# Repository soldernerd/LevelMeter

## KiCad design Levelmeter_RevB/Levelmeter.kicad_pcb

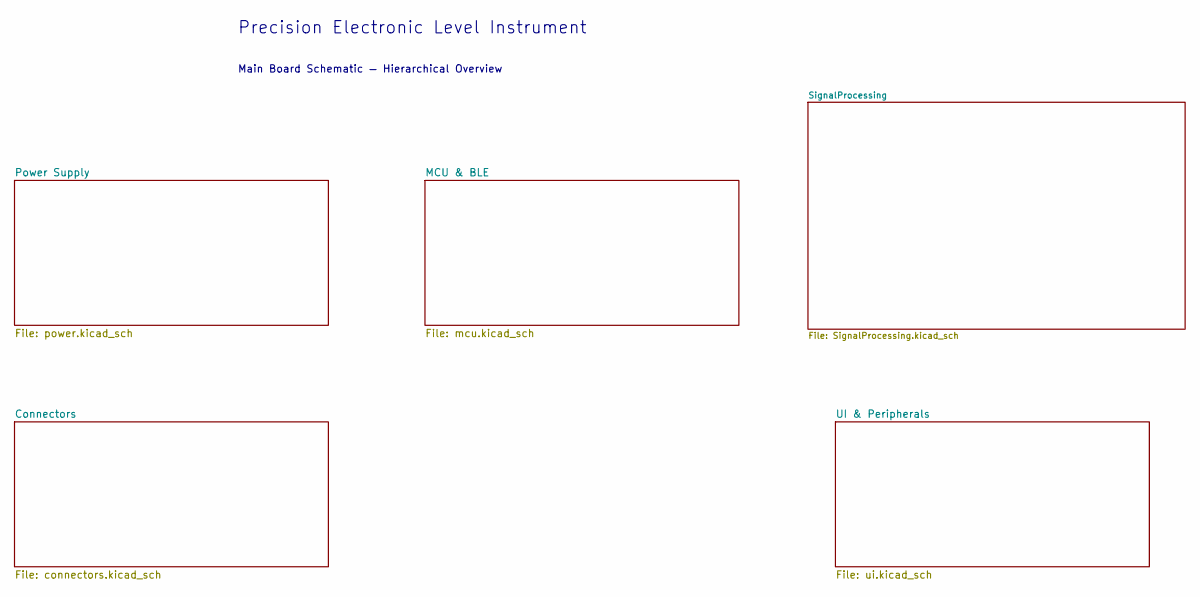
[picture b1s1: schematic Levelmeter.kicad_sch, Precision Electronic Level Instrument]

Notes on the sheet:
Main Board Schematic — Hierarchical Overview
Precision Electronic Level Instrument

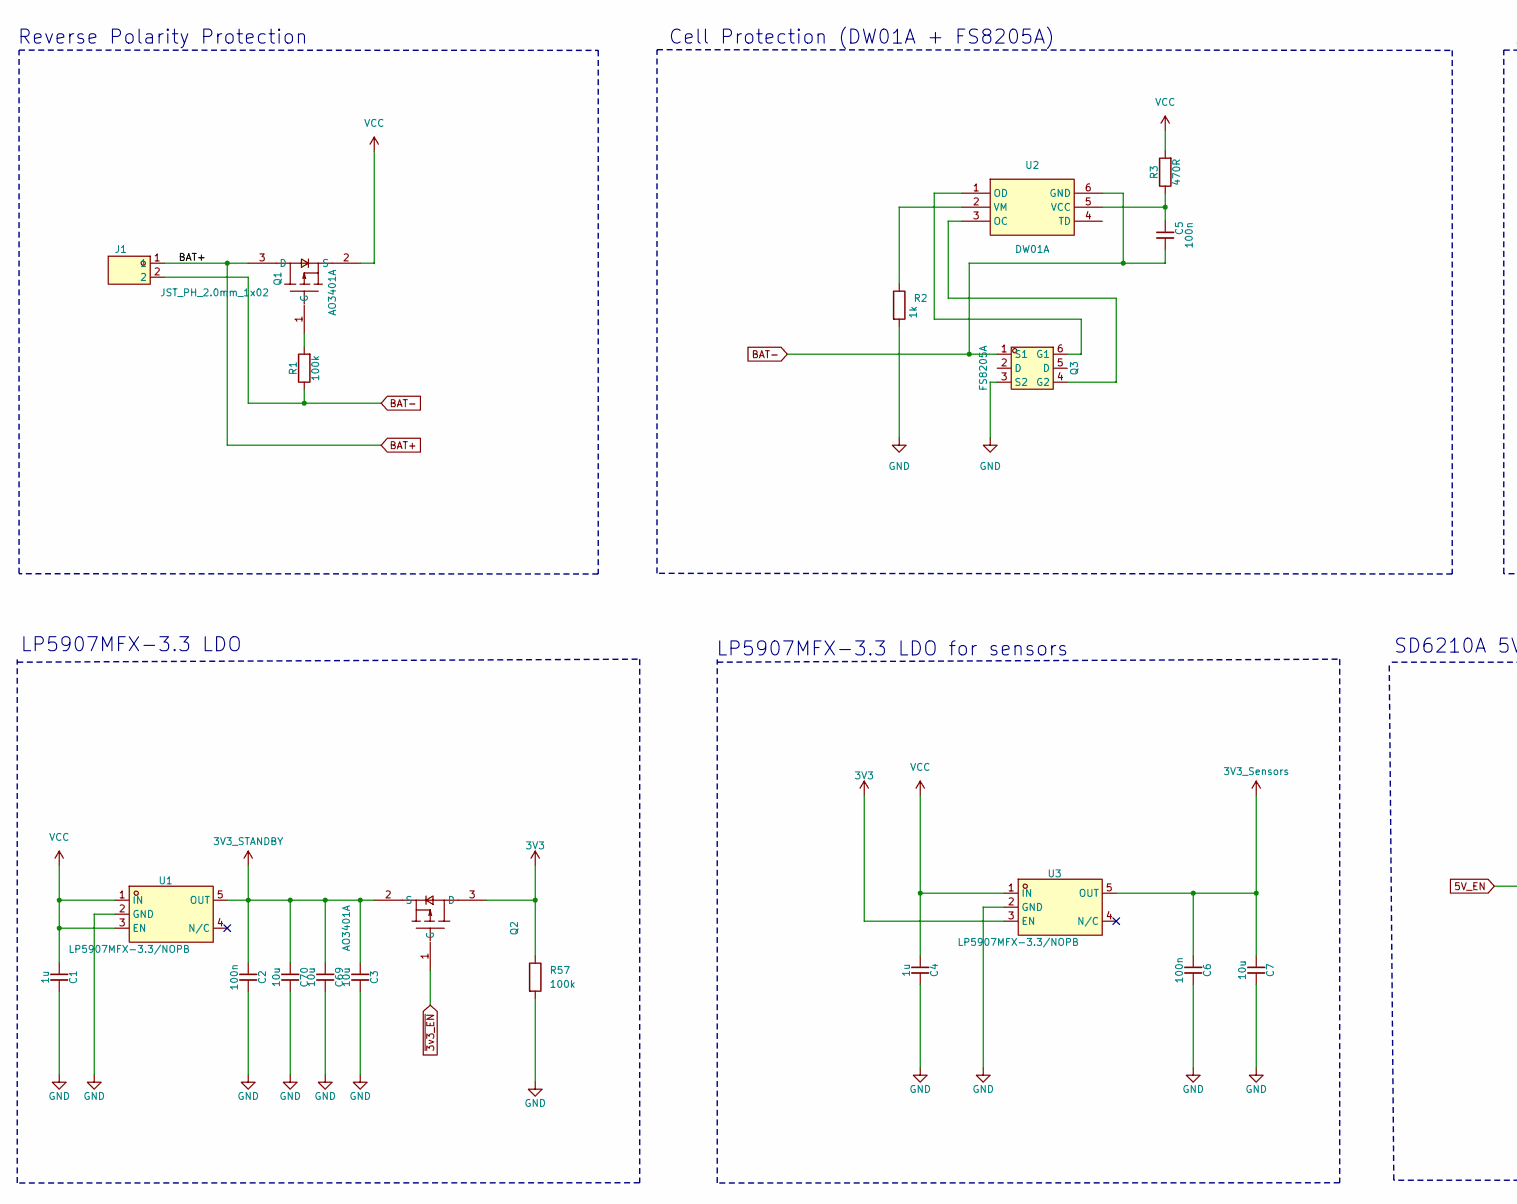
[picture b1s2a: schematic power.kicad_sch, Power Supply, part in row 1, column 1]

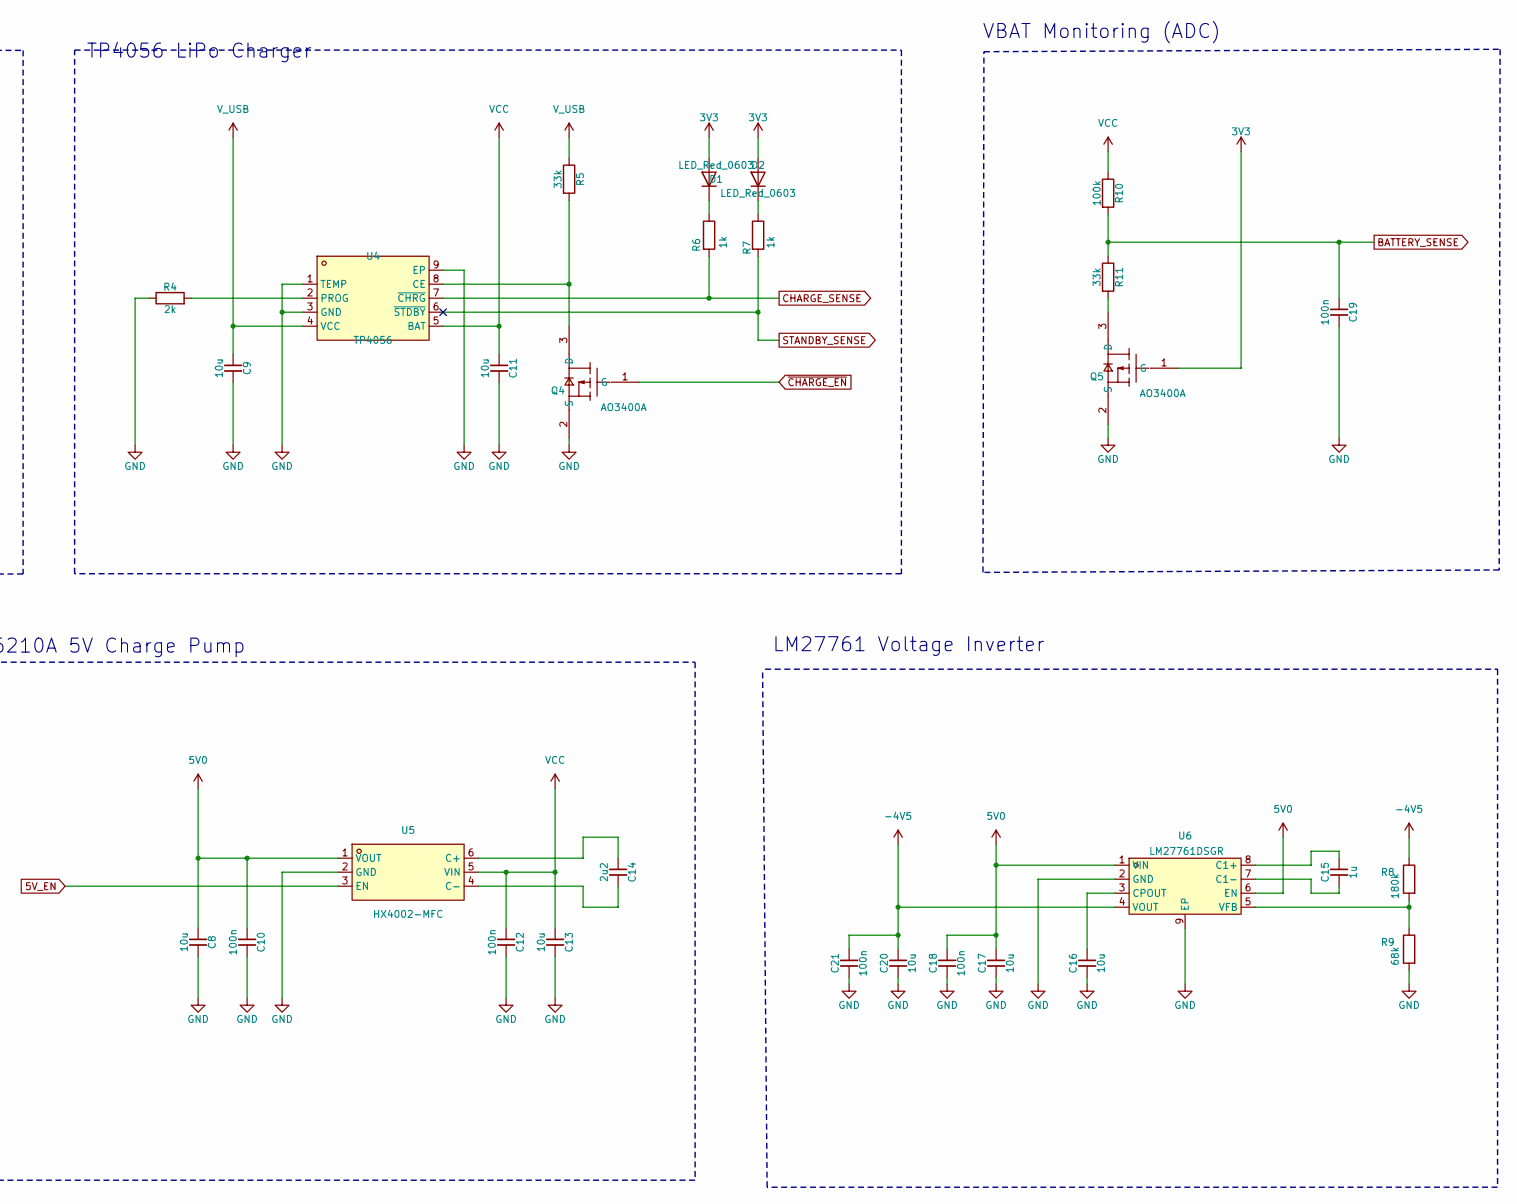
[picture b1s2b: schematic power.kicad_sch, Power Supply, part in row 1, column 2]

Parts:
C1, C4, C15: 1u; C_0805; Voltage 50V; MPN CL21B105KBFNNNE; LCSC C28323
C2, C5, C6, C10, C12, C18, C19, C21: 100n; C_0603; Voltage 50V; MPN CC0603KRX7R9BB104; LCSC C14663
C3, C7, C8, C9, C11, C13, C16, C17, C20, C69, C70: 10u; C_0805; Voltage 50V; MPN GRM21BR61H106KE43L; LCSC C440198
C14: 2u2; C_0805; Voltage 50V; MPN CL21A225KBQNNNE; LCSC C377773
D1, D2: LED_Red_0603; LED_0603; MPN KT-0603R; LCSC C2286
J1: JST_PH_2.0mm_1x02; MPN B2B-PH-K-S; LCSC C131337
Q1, Q2: AO3401A; SOT-23-3; MPN AO3401A; LCSC C15127
Q3: FS8205A; SOT-23-6; MPN FS8205A; LCSC C2830320
Q4, Q5: AO3400A; SOT-23-3; MPN AO3400A; LCSC C20917
R1, R10, R57: 100k; R_0603; MPN 0603WAF1003T5E; LCSC C25803
R2, R6, R7: 1k; R_0603; MPN 0603WAF1001T5E; LCSC C21190
R3: 470R; R_0603; MPN 0603WAF4700T5E; LCSC C23179
R4: 2k; R_0603; MPN 0603WAF2001T5E; LCSC C22975
R5, R11: 33k; R_0603; MPN 0603WAF3302T5E; LCSC C4216
R8: 180k; R_0603; MPN 0603WAF1803T5E; LCSC C22827
R9: 68k; R_0603; MPN 0603WAF6802T5E; LCSC C23231
U1, U3: LP5907MFX-3.3/NOPB; SOT-23-5; MPN LP5907MFX-3.3/NOPB; LCSC C80670
U2: DW01A; SOT-23-6; MPN DW01A; LCSC C351410
U4: TP4056; ESOP-8; MPN TP4056; LCSC C382139
U5: HX4002-MFC; SOT-23-6; MPN HX4002-MFC; LCSC C172354
U6: LM27761DSGR; WSON-8-2x2-EP; MPN LM27761DSGR; LCSC C129351

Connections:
3V3: D1.2 (A), D2.2 (A), Q2.3 (D), Q5.1 (G), R57.1, U3.3 (EN); also elsewhere on the board
3V3_STANDBY: C2.1, C3.1, C69.1, C70.1, Q2.2 (S), U1.5 (OUT); also elsewhere on the board
3V3_Sensors: C6.1, C7.1, U3.5 (OUT); also elsewhere on the board
5V0: C8.1, C10.1, C17.1, C18.1, U5.1 (VOUT), U6.1 (VIN), U6.6 (EN); also elsewhere on the board
5V_EN: U5.3 (EN); also elsewhere on the board
~3v3_EN: Q2.1 (G); also elsewhere on the board
-4V5: C20.1, C21.1, R8.1, U6.4 (VOUT); also elsewhere on the board
BAT+: J1.1, Q1.3 (D)
BAT-: C5.2, J1.2, Q3.1 (S1), R1.1, U2.6 (GND)
BATTERY_SENSE: C19.1, R10.2, R11.1; also elsewhere on the board
CHARGE_SENSE: R6.2, U4.7 (~CHRG); also elsewhere on the board
GND: C1.2, C2.2, C3.2, C4.2, C6.2, C7.2, C8.2, C9.2, C10.2, C11.2, C12.2, C13.2, C16.2, C17.2, C18.2, C19.2, C20.2, C21.2, C69.2, C70.2, Q3.3 (S2), Q4.2 (S), Q5.2 (S), R2.2, R4.1, R9.2, R57.2, U1.2 (GND), U3.2 (GND), U4.1 (TEMP), U4.3 (GND), U4.9 (EP), U5.2 (GND), U6.2 (GND), U6.9 (EP); also elsewhere on the board
unnamed: D1.1 (K), R6.1
unnamed: D2.1 (K), R7.1
unnamed: Q1.1 (G), R1.2
unnamed: Q3.6 (G1), U2.1 (OD)
unnamed: Q3.4 (G2), U2.3 (OC)
unnamed: Q4.3 (D), R5.2, U4.8 (CE)
unnamed: Q5.3 (D), R11.2
unnamed: C5.1, R3.1, U2.5 (VCC)
unnamed: R2.1, U2.2 (VM)
unnamed: R4.2, U4.2 (PROG)
unnamed: C14.1, U5.6 (C+)
unnamed: C14.2, U5.4 (C-)
unnamed: C15.1, U6.8 (C1+)
unnamed: C15.2, U6.7 (C1-)
unnamed: C16.1, U6.3 (CPOUT)
unnamed: R8.2, R9.1, U6.5 (VFB)
STANDBY_SENSE: R7.2, U4.6 (~STDBY); also elsewhere on the board
VCC: C1.1, C4.1, C11.1, C12.1, C13.1, Q1.2 (S), R3.2, R10.1, U1.1 (IN), U1.3 (EN), U3.1 (IN), U4.5 (BAT), U5.5 (VIN)
V_USB: C9.1, R5.1, U4.4 (VCC); also elsewhere on the board
~CHARGE_EN: Q4.1 (G); also elsewhere on the board

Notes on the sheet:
LM27761 Voltage Inverter
LP5907MFX-3.3 LDO
VBAT Monitoring (ADC)
Cell Protection (DW01A + FS8205A)
TP4056 LiPo Charger
Reverse Polarity Protection
SD6210A 5V Charge Pump
LP5907MFX-3.3 LDO for sensors

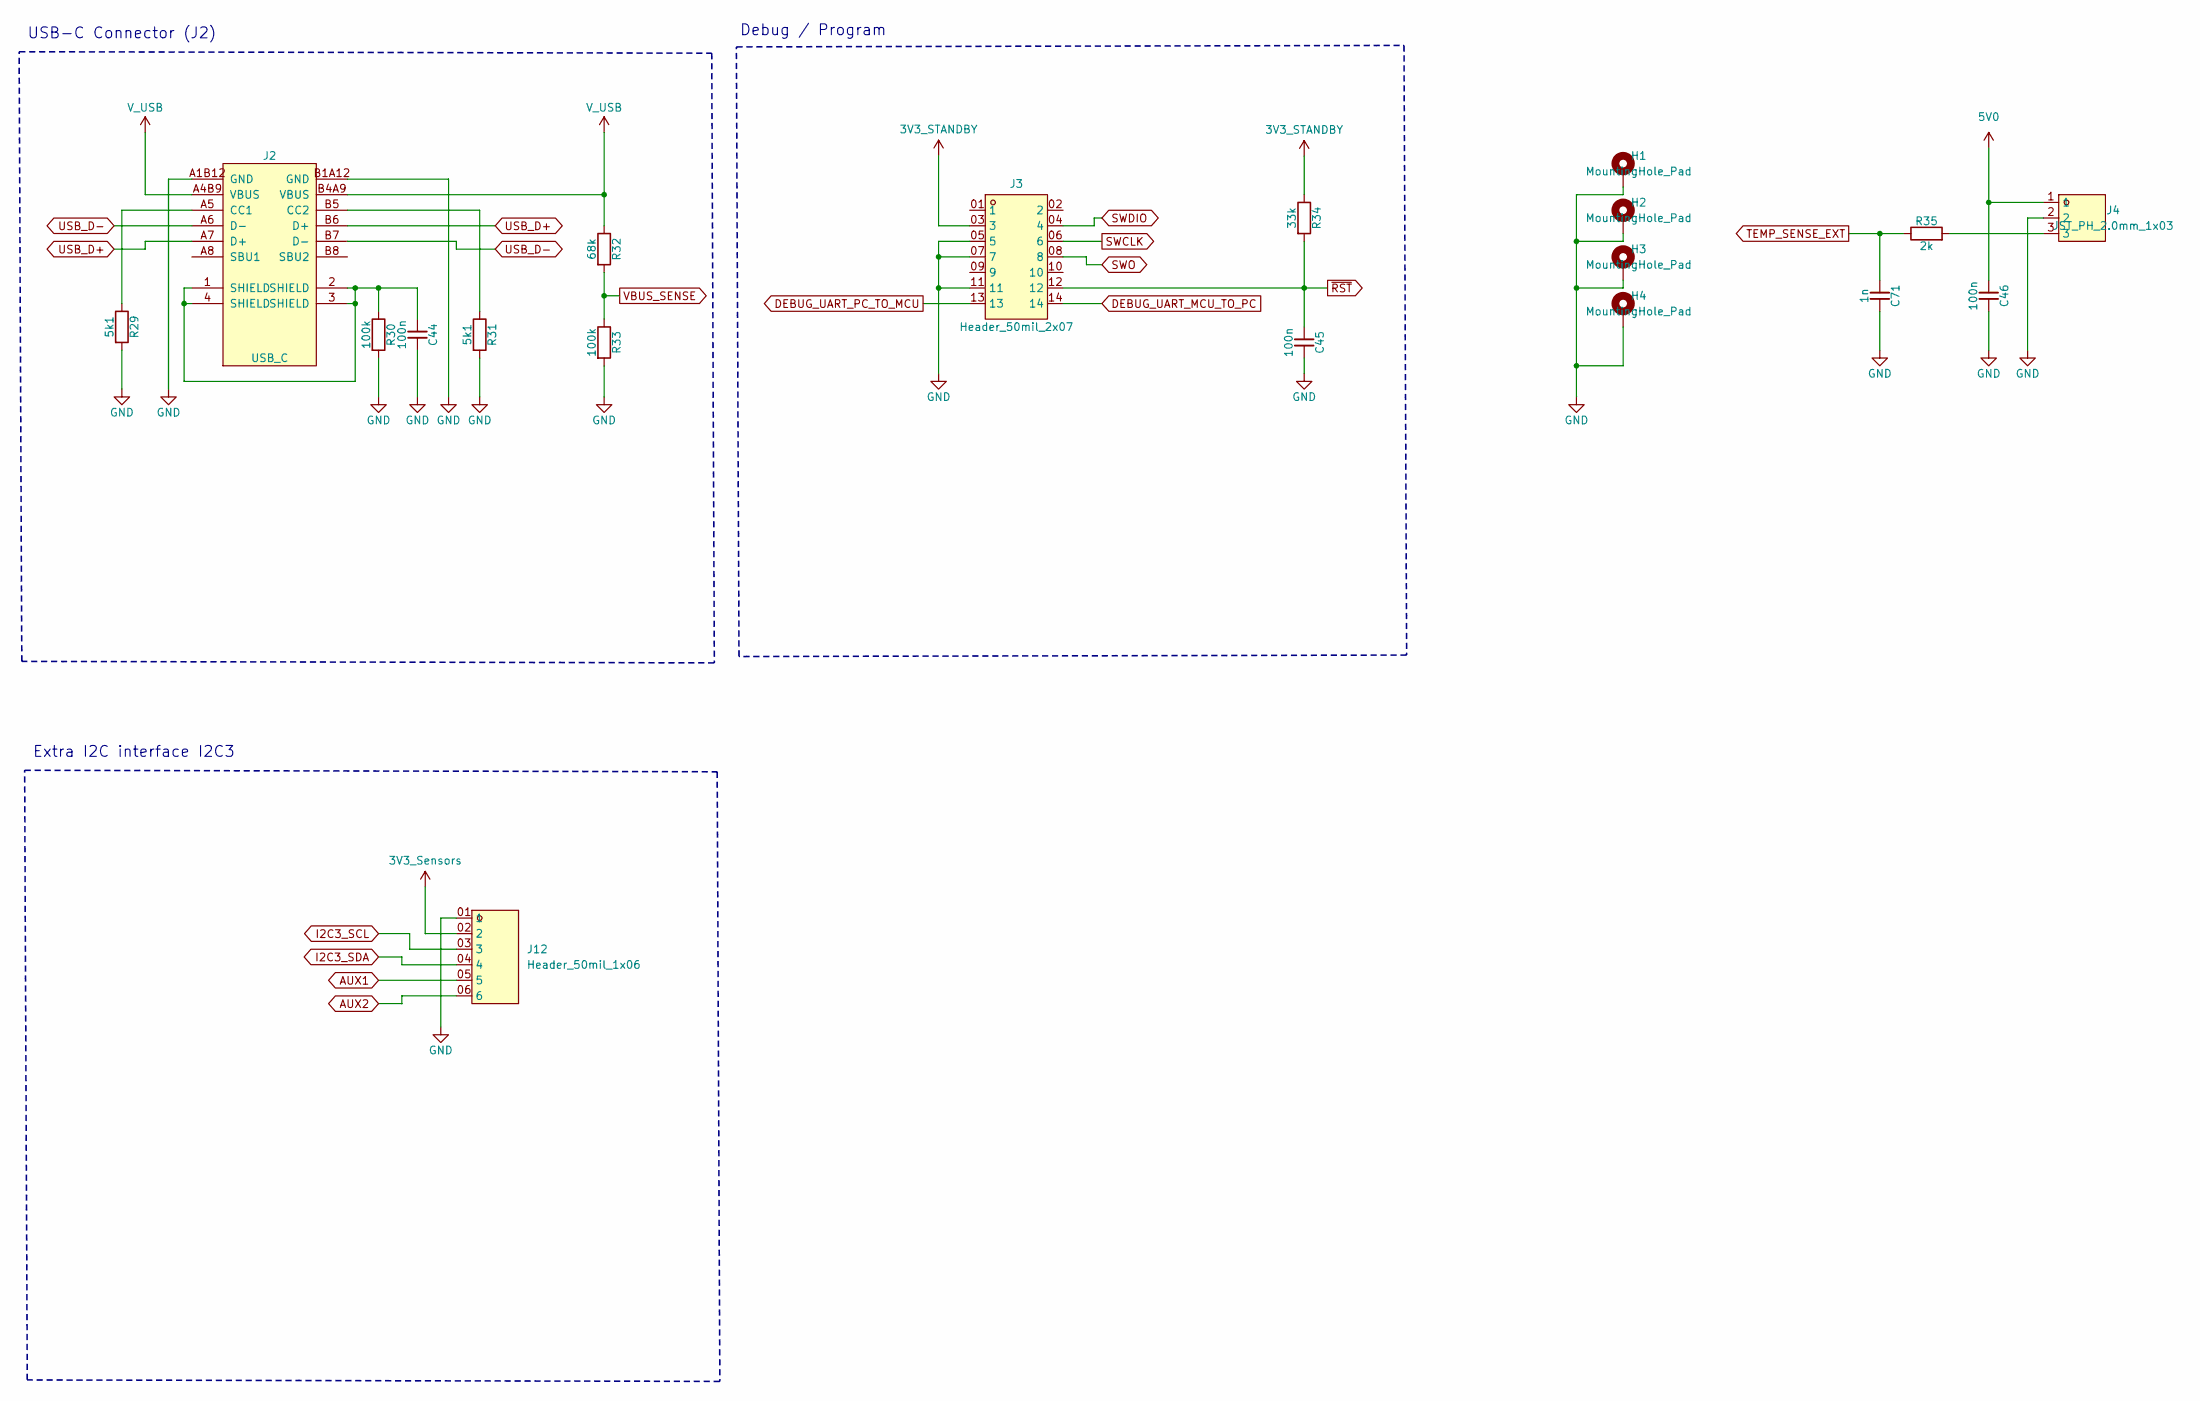
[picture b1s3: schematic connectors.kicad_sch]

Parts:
C44, C45, C46: 100n; C_0603; Voltage 50V; MPN CC0603KRX7R9BB104; LCSC C14663
C71: 1n; C_0603; Voltage 50V; MPN CL10B102KB8NNNC; LCSC C1588
H1, H2, H3, H4: MountingHole_Pad; MountingHole_3.2mm
J2: USB_C; MPN TYPE-C-31-M-12; LCSC C165948
J3: Header_50mil_2x07; LCSC C5563894
J4: JST_PH_2.0mm_1x03; MPN B3B-PH-K-S; LCSC C131339
J12: Header_50mil_1x06
R29, R31: 5k1; R_0603; MPN 0603WAF5101T5E; LCSC C23186
R30, R33: 100k; R_0603; MPN 0603WAF1003T5E; LCSC C25803
R32: 68k; R_0603; MPN 0603WAF6802T5E; LCSC C23231
R34: 33k; R_0603; MPN 0603WAF3302T5E; LCSC C4216
R35: 2k; R_0603; MPN 0603WAF2001T5E; LCSC C22975

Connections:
3V3_STANDBY: J3.03 (3), R34.1; also elsewhere on the board
3V3_Sensors: J12.02 (2); also elsewhere on the board
5V0: C46.1, J4.1; also elsewhere on the board
AUX1: J12.05 (5); also elsewhere on the board
AUX2: J12.06 (6); also elsewhere on the board
DEBUG_UART_MCU_TO_PC: J3.14; also elsewhere on the board
DEBUG_UART_PC_TO_MCU: J3.13; also elsewhere on the board
GND: C44.2, C45.2, C46.2, C71.2, H1.1 (1_1), H2.1 (1_1), H3.1 (1_1), H4.1 (1_1), J2.A1B12 (GND), J2.B1A12 (GND), J3.05 (5), J3.07 (7), J3.11, J4.2, J12.01 (1), R29.2, R30.2, R31.2, R33.2; also elsewhere on the board
I2C3_SCL: J12.03 (3); also elsewhere on the board
I2C3_SDA: J12.04 (4); also elsewhere on the board
unnamed: C44.1, J2.1 (SHIELD), J2.2 (SHIELD), J2.3 (SHIELD), J2.4 (SHIELD), R30.1
unnamed: J2.A5 (CC1), R29.1
unnamed: J2.B5 (CC2), R31.1
unnamed: J4.3, R35.2
SWCLK: J3.06 (6); also elsewhere on the board
SWDIO: J3.04 (4); also elsewhere on the board
SWO: J3.08 (8); also elsewhere on the board
TEMP_SENSE_EXT: C71.1, R35.1; also elsewhere on the board
USB_D+: J2.A7 (D+), J2.B6 (D+); also elsewhere on the board
USB_D-: J2.A6 (D-), J2.B7 (D-); also elsewhere on the board
VBUS_SENSE: R32.2, R33.1; also elsewhere on the board
V_USB: J2.A4B9 (VBUS), J2.B4A9 (VBUS), R32.1; also elsewhere on the board
~RST: C45.1, J3.12, R34.2; also elsewhere on the board

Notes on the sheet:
Extra I2C interface I2C3
USB-C Connector (J2)
Debug / Program

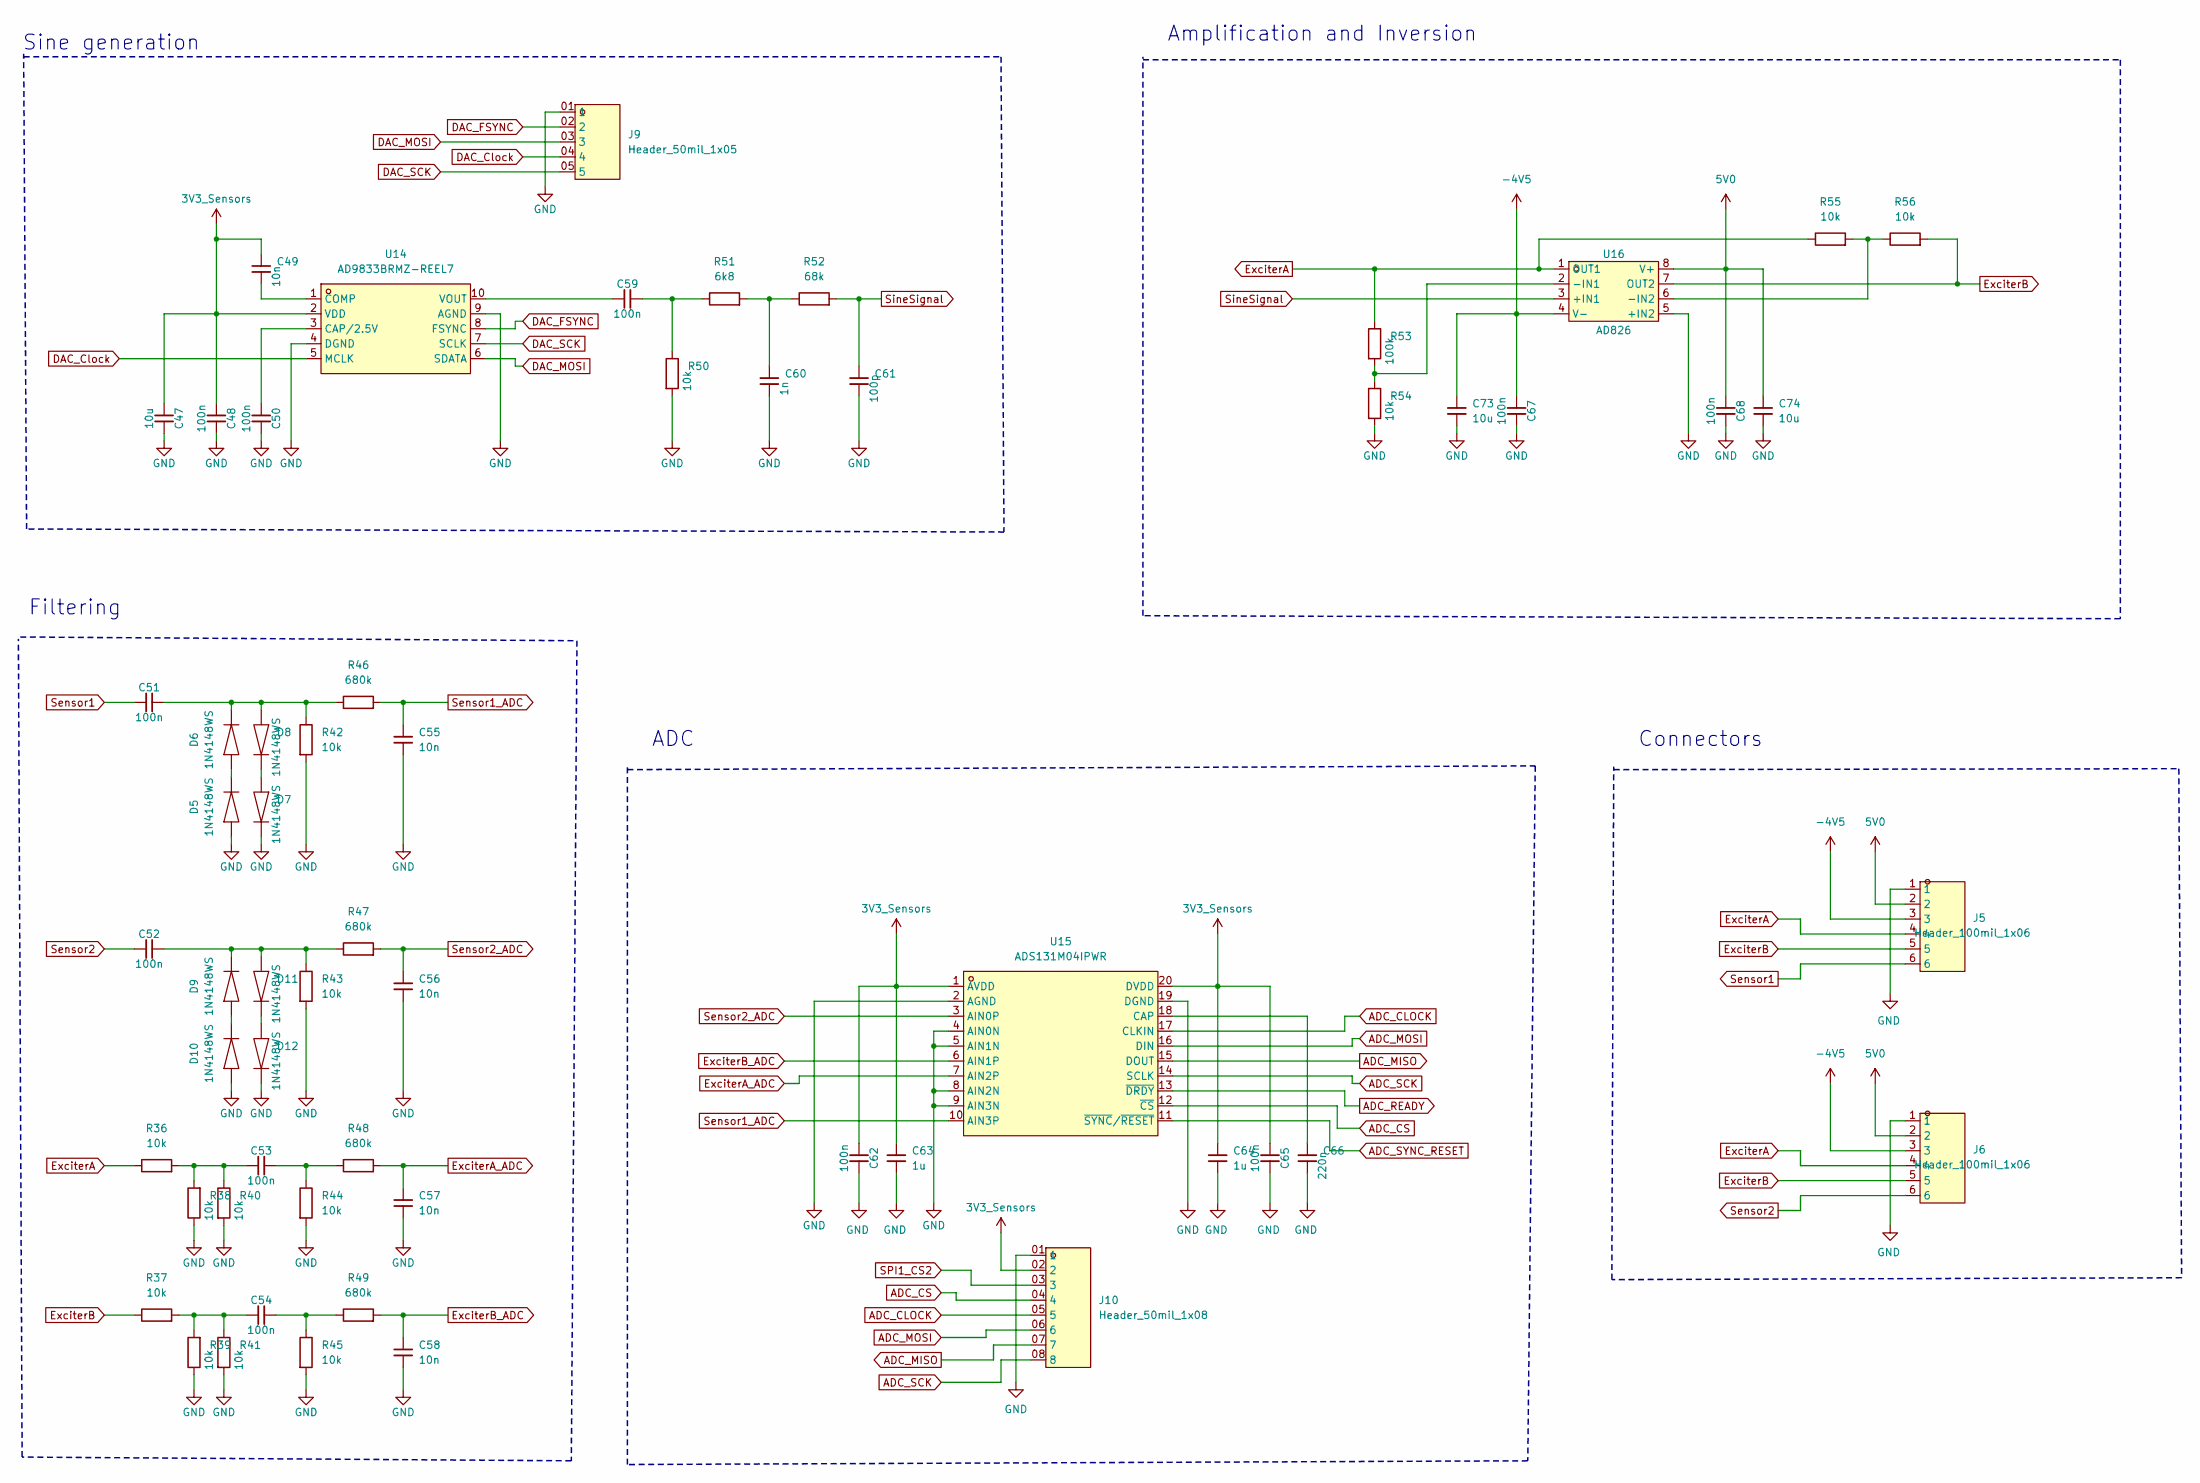
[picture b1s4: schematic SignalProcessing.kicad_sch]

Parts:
C47, C73, C74: 10u; C_0805; Voltage 50V; MPN GRM21BR61H106KE43L; LCSC C440198
C48, C50, C51, C52, C53, C54, C59, C62, C65, C67, C68: 100n; C_0603; Voltage 50V; MPN CC0603KRX7R9BB104; LCSC C14663
C49, C55, C56, C57, C58: 10n; C_0603; Voltage 50V; MPN 0603B103K500NT; LCSC C57112
C60: 1n; C_0603; Voltage 50V; MPN CL10B102KB8NNNC; LCSC C1588
C61: 100p; C_0603; Voltage 50V; MPN CL10C101JB8NNNC; LCSC C14858
C63, C64: 1u; C_0805; Voltage 50V; MPN CL21B105KBFNNNE; LCSC C28323
C66: 220n; C_0603; Voltage 25V; MPN CL10B224KA8NNNC; LCSC C21120
D5, D6, D7, D8, D9, D10, D11, D12: 1N4148WS; SOD-323; MPN 1N4148WS; LCSC C2128
J5, J6: Header_100mil_1x06; MPN A2541WV-6P; LCSC C225481
J9: Header_50mil_1x05
J10: Header_50mil_1x08
R36, R37, R38, R39, R40, R41, R42, R43, R44, R45, R50, R55, R56: 10k; R_0603; MPN 0603WAF1002T5E; LCSC C25804
R46, R47, R48, R49: 680k; R_0603; MPN 0603WAF6803T5E; LCSC C25822
R51: 6k8; R_0603; MPN 0603WAF6801T5E; LCSC C23212
R52: 68k; R_0603; MPN 0603WAF6802T5E; LCSC C23231
R53: 100k; R_0805; MPN 0805W8F1003T5E; LCSC C149504
R54: 10k; R_0805; MPN 0805W8F1002T5E; LCSC C17414
U14: AD9833BRMZ-REEL7; MSOP-10; MPN AD9833BRMZ-REEL7; LCSC C9652
U15: ADS131M04IPWR; TSSOP-20; MPN ADS131M04IPWR; LCSC C2862562
U16: AD826; SOIC-8; MPN AD826ARZ-REEL7; LCSC C114171

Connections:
3V3_Sensors: C47.1, C48.1, C49.1, C62.1, C63.1, C64.1, C65.1, J10.02 (2), U14.2 (VDD), U15.1 (AVDD), U15.20 (DVDD); also elsewhere on the board
5V0: C68.1, C74.1, J5.2, J6.2, U16.8 (V+); also elsewhere on the board
-4V5: C67.1, C73.1, J5.3, J6.3, U16.4 (V-); also elsewhere on the board
ADC_CLOCK: J10.05 (5), U15.17 (CLKIN); also elsewhere on the board
ADC_CS: J10.04 (4), U15.12 (~CS); also elsewhere on the board
ADC_MISO: J10.07 (7), U15.15 (DOUT); also elsewhere on the board
ADC_MOSI: J10.06 (6), U15.16 (DIN); also elsewhere on the board
ADC_READY: U15.13 (~DRDY); also elsewhere on the board
ADC_SCK: J10.08 (8), U15.14 (SCLK); also elsewhere on the board
ADC_SYNC_RESET: U15.11 (~SYNC/~RESET); also elsewhere on the board
DAC_Clock: J9.04 (4), U14.5 (MCLK); also elsewhere on the board
DAC_FSYNC: J9.02 (2), U14.8 (FSYNC); also elsewhere on the board
DAC_MOSI: J9.03 (3), U14.6 (SDATA); also elsewhere on the board
DAC_SCK: J9.05 (5), U14.7 (SCLK); also elsewhere on the board
ExciterA: J5.4, J6.4, R36.1, R53.1, R55.1, U16.1 (OUT1)
ExciterA_ADC: C57.1, R48.2, U15.7 (AIN2P)
ExciterB: J5.5, J6.5, R37.1, R56.2, U16.7 (OUT2)
ExciterB_ADC: C58.1, R49.2, U15.6 (AIN1P)
GND: C47.2, C48.2, C50.2, C55.2, C56.2, C57.2, C58.2, C60.2, C61.2, C62.2, C63.2, C64.2, C65.2, C66.2, C67.2, C68.2, C73.2, C74.2, D5.2 (A), D7.1 (K), D10.2 (A), D12.1 (K), J5.1, J6.1, J9.01 (1), J10.01 (1), R38.1, R39.1, R40.2, R41.2, R42.2, R43.2, R44.2, R45.2, R50.2, R54.2, U14.4 (DGND), U14.9 (AGND), U15.2 (AGND), U15.4 (AIN0N), U15.5 (AIN1N), U15.8 (AIN2N), U15.9 (AIN3N), U15.19 (DGND), U16.5 (+IN2); also elsewhere on the board
unnamed: C53.1, R36.2, R38.2, R40.1
unnamed: C53.2, R44.1, R48.1
unnamed: C54.1, R37.2, R39.2, R41.1
unnamed: C54.2, R45.1, R49.1
unnamed: C59.2, R50.1, R51.1
unnamed: C60.1, R51.2, R52.1
unnamed: D5.1 (K), D6.2 (A)
unnamed: C51.2, D6.1 (K), D8.2 (A), R42.1, R46.1
unnamed: D7.2 (A), D8.1 (K)
unnamed: D9.2 (A), D10.1 (K)
unnamed: C52.2, D9.1 (K), D11.2 (A), R43.1, R47.1
unnamed: D11.1 (K), D12.2 (A)
unnamed: C50.1, U14.3 (CAP/2.5V)
unnamed: C49.2, U14.1 (COMP)
unnamed: C59.1, U14.10 (VOUT)
unnamed: C66.1, U15.18 (CAP)
unnamed: R53.2, R54.1, U16.2 (-IN1)
unnamed: R55.2, R56.1, U16.6 (-IN2)
SPI1_CS2: J10.03 (3); also elsewhere on the board
Sensor1: C51.1, J5.6
Sensor1_ADC: C55.1, R46.2, U15.10 (AIN3P)
Sensor2: C52.1, J6.6
Sensor2_ADC: C56.1, R47.2, U15.3 (AIN0P)
SineSignal: C61.1, R52.2, U16.3 (+IN1)

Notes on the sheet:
ADC
Connectors
Filtering
Amplification and Inversion
Sine generation

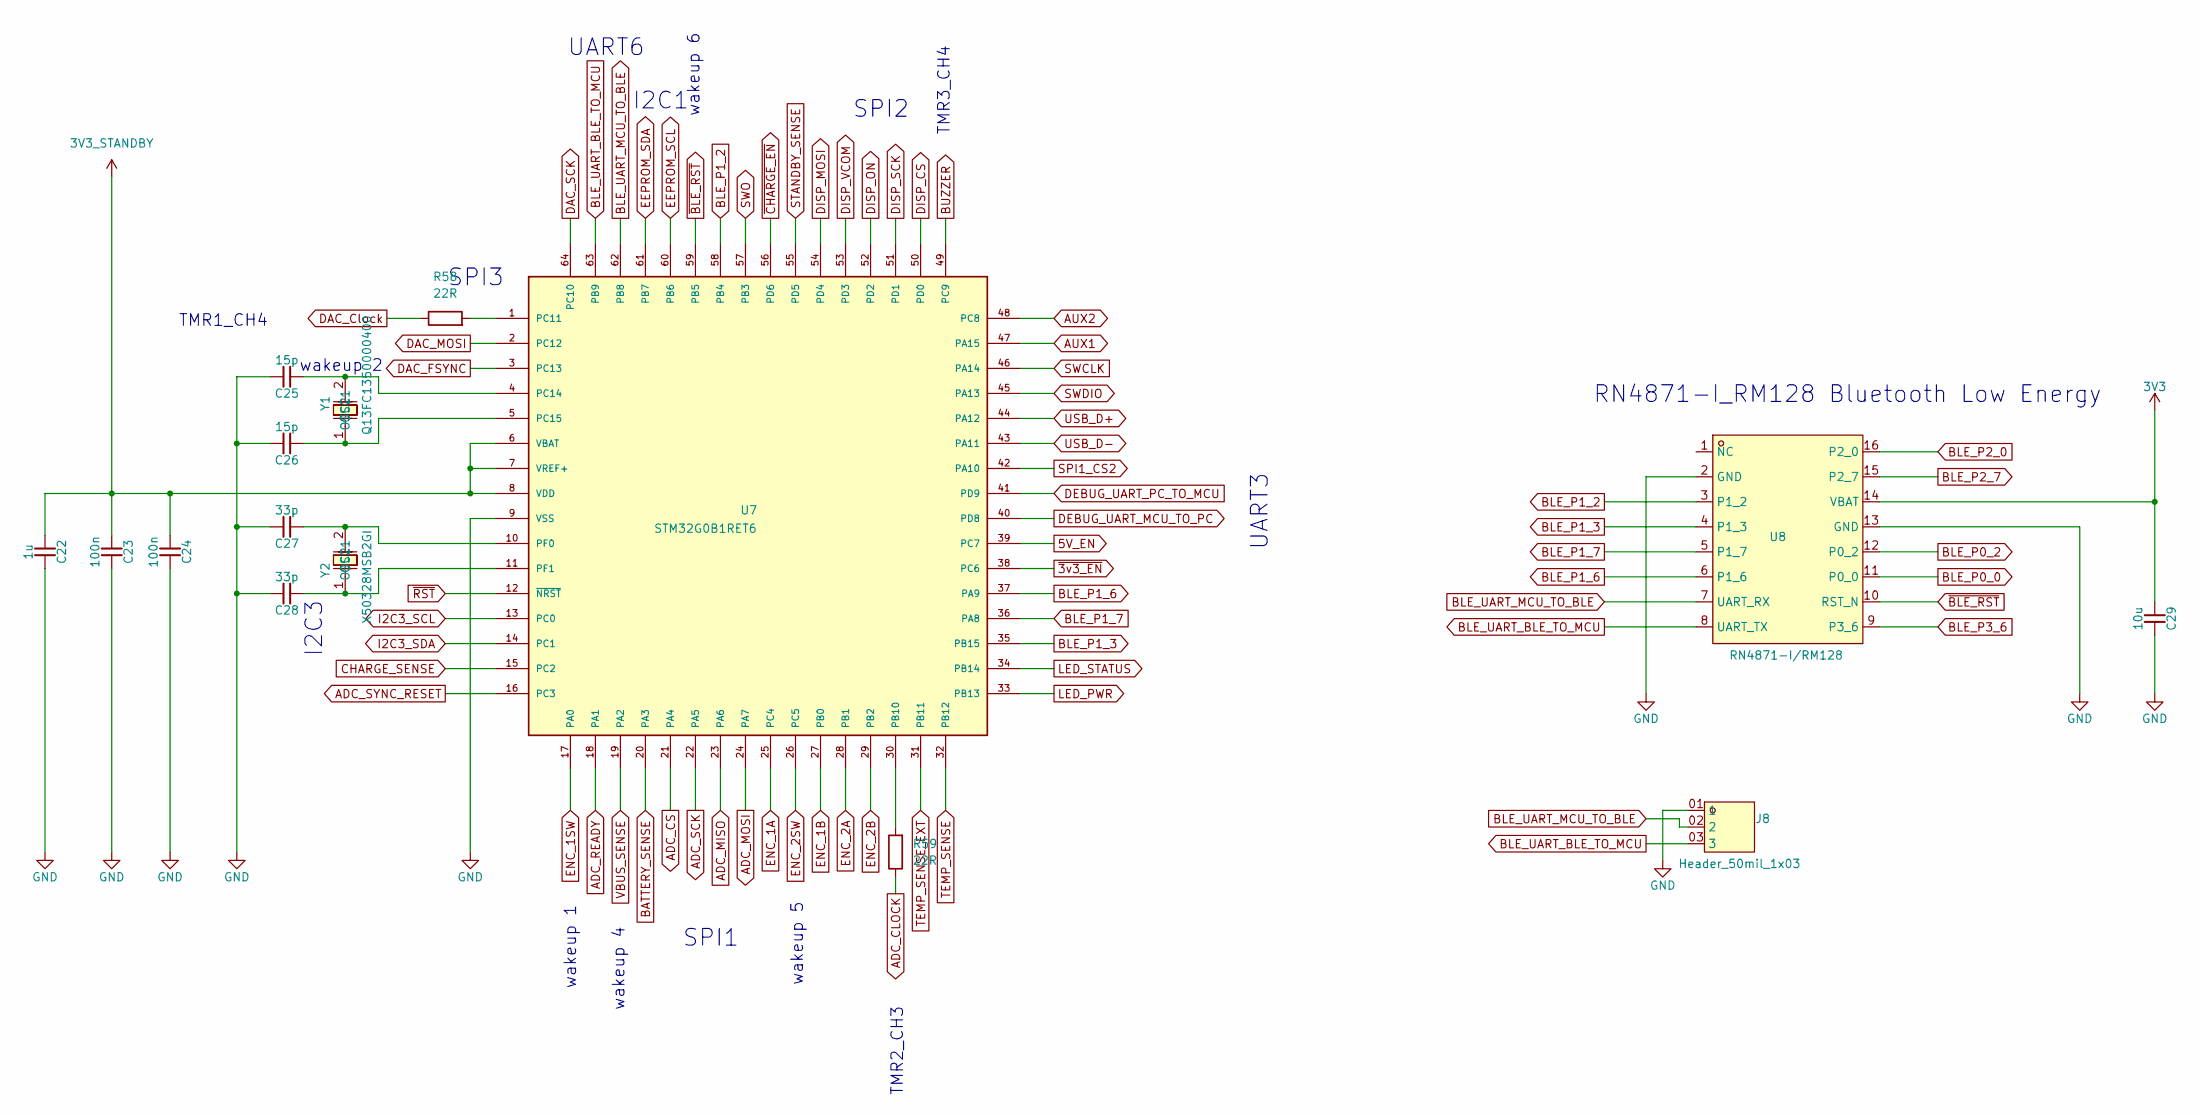
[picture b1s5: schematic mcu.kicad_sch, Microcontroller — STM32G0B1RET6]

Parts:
C22: 1u; C_0805; Voltage 50V; MPN CL21B105KBFNNNE; LCSC C28323
C23, C24: 100n; C_0603; Voltage 50V; MPN CC0603KRX7R9BB104; LCSC C14663
C25, C26: 15p; C_0603; Voltage 50V; MPN CL10C150JB8NNNC; LCSC C1644
C27, C28: 33p; C_0603; Voltage 50V; MPN CL10C330JB8NNNC; LCSC C1663
C29: 10u; C_0805; Voltage 50V; MPN GRM21BR61H106KE43L; LCSC C440198
J8: Header_50mil_1x03; MPN HC-PZ127-7.2L-1x3PZ; LCSC C42162998
R58, R59: 22R; R_0603; MPN 0603WAF220JT5E; LCSC C23345
U7: STM32G0B1RET6; LQFP-64; LCSC C2829307
U8: RN4871-I/RM128; RN4871; MPN RN4871-I/RM128; LCSC C633941
Y1: Q13FC1350000400; CRYSTAL-3215; MPN Q13FC1350000400; LCSC C32346
Y2: X50328MSB2GI; CRYSTAL-3225; MPN X50328MSB2GI; LCSC C115962

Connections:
3V3: C29.1, U8.14 (VBAT); also elsewhere on the board
3V3_STANDBY: C22.1, C23.1, C24.1, U7.6 (VBAT), U7.7 (VREF+), U7.8 (VDD); also elsewhere on the board
5V_EN: U7.39 (PC7); also elsewhere on the board
~3v3_EN: U7.38 (PC6); also elsewhere on the board
ADC_CLOCK: R59.1; also elsewhere on the board
ADC_CS: U7.21 (PA4); also elsewhere on the board
ADC_MISO: U7.23 (PA6); also elsewhere on the board
ADC_MOSI: U7.24 (PA7); also elsewhere on the board
ADC_READY: U7.18 (PA1); also elsewhere on the board
ADC_SCK: U7.22 (PA5); also elsewhere on the board
ADC_SYNC_RESET: U7.16 (PC3); also elsewhere on the board
AUX1: U7.47 (PA15); also elsewhere on the board
AUX2: U7.48 (PC8); also elsewhere on the board
BATTERY_SENSE: U7.20 (PA3); also elsewhere on the board
BLE_P0_0: U8.11 (P0_0)
BLE_P0_2: U8.12 (P0_2)
BLE_P1_2: U7.58 (PB4), U8.3 (P1_2)
BLE_P1_3: U7.35 (PB15), U8.4 (P1_3)
BLE_P1_6: U7.37 (PA9), U8.6 (P1_6)
BLE_P1_7: U7.36 (PA8), U8.5 (P1_7)
BLE_P2_0: U8.16 (P2_0)
BLE_P2_7: U8.15 (P2_7)
BLE_P3_6: U8.9 (P3_6)
BLE_UART_BLE_TO_MCU: J8.03 (3), U7.63 (PB9), U8.8 (UART_TX)
BLE_UART_MCU_TO_BLE: J8.02 (2), U7.62 (PB8), U8.7 (UART_RX)
BUZZER: U7.49 (PC9); also elsewhere on the board
CHARGE_SENSE: U7.15 (PC2); also elsewhere on the board
DAC_Clock: R58.1; also elsewhere on the board
DAC_FSYNC: U7.3 (PC13); also elsewhere on the board
DAC_MOSI: U7.2 (PC12); also elsewhere on the board
DAC_SCK: U7.64 (PC10); also elsewhere on the board
DEBUG_UART_MCU_TO_PC: U7.40 (PD8); also elsewhere on the board
DEBUG_UART_PC_TO_MCU: U7.41 (PD9); also elsewhere on the board
DISP_CS: U7.50 (PD0); also elsewhere on the board
DISP_MOSI: U7.54 (PD4); also elsewhere on the board
DISP_ON: U7.52 (PD2); also elsewhere on the board
DISP_SCK: U7.51 (PD1); also elsewhere on the board
DISP_VCOM: U7.53 (PD3); also elsewhere on the board
EEPROM_SCL: U7.60 (PB6); also elsewhere on the board
EEPROM_SDA: U7.61 (PB7); also elsewhere on the board
ENC_1A: U7.25 (PC4); also elsewhere on the board
ENC_1B: U7.27 (PB0); also elsewhere on the board
ENC_1SW: U7.17 (PA0); also elsewhere on the board
ENC_2A: U7.28 (PB1); also elsewhere on the board
ENC_2B: U7.29 (PB2); also elsewhere on the board
ENC_2SW: U7.26 (PC5); also elsewhere on the board
GND: C22.2, C23.2, C24.2, C25.2, C26.2, C27.2, C28.2, C29.2, J8.01 (1), U7.9 (VSS), U8.2 (GND), U8.13 (GND); also elsewhere on the board
I2C3_SCL: U7.13 (PC0); also elsewhere on the board
I2C3_SDA: U7.14 (PC1); also elsewhere on the board
LED_PWR: U7.33 (PB13); also elsewhere on the board
LED_STATUS: U7.34 (PB14); also elsewhere on the board
unnamed: R59.2, U7.30 (PB10)
unnamed: R58.2, U7.1 (PC11)
unnamed: C25.1, U7.4 (PC14), Y1.2 (OSC2)
unnamed: C26.1, U7.5 (PC15), Y1.1 (OSC1)
unnamed: C27.1, U7.10 (PF0), Y2.2 (OSC2)
unnamed: C28.1, U7.11 (PF1), Y2.1 (OSC1)
SPI1_CS2: U7.42 (PA10); also elsewhere on the board
STANDBY_SENSE: U7.55 (PD5); also elsewhere on the board
SWCLK: U7.46 (PA14); also elsewhere on the board
SWDIO: U7.45 (PA13); also elsewhere on the board
SWO: U7.57 (PB3); also elsewhere on the board
TEMP_SENSE: U7.32 (PB12); also elsewhere on the board
TEMP_SENSE_EXT: U7.31 (PB11); also elsewhere on the board
USB_D+: U7.44 (PA12); also elsewhere on the board
USB_D-: U7.43 (PA11); also elsewhere on the board
VBUS_SENSE: U7.19 (PA2); also elsewhere on the board
~BLE_RST: U7.59 (PB5), U8.10 (RST_N)
~CHARGE_EN: U7.56 (PD6); also elsewhere on the board
~RST: U7.12 (~NRST); also elsewhere on the board

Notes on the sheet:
SPI1
TMR2_CH3
wakeup 2
wakeup 1
TMR3_CH4
TMR1_CH4
SPI2
wakeup 5
I2C3
wakeup 4
I2C1
UART6
wakeup 6
RN4871-I_RM128 Bluetooth Low Energy
UART3
SPI3
